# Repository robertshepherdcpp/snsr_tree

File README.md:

# snsr_tree
a tree with all the sensors you need to stay healthy!

## inspiration
- i have always wanted some sensors for my room, however, they are expensive and involve constantly checking the readings.
- so i thought it would be cool to make my own, where all these sensors are merged into one thing — and if certain levels were too high, it would actually tell me to change them!
- i wanted it to be something that sits in my room, so i decided to make it the shape of a tree (to blend in with the plants on my desk).

## how to use
1. get the PCB and case printed, and buy all the parts (listed in the BOM — total cost: $82.23)
2. paint the case green as shown in the 3D renders
3. download the audio files (mp3) from this repository and save them onto an SD card (32GB)
4. insert the SD card into the SD card holder on the PCB
5. assemble the case using screws, which also go through the PCB
6. plug into a computer and flash the firmware (in this repository) to the XIAO-ESP32-C6 — easiest via the Arduino IDE
7. keep plugged into the computer, as it is the project's power source
8. use the project and listen out for warnings!

## what it is / how it works
- the snsr_tree takes readings of different environmental levels: CO2, humidity, temperature, and light
- based on those readings, it will alert you to change certain levels — or in some cases do it for you (e.g. when it's too dark)
- keeping you informed about the conditions in your room!
  
## features
- WiFi communication for RTC (real-time clock sync)
- I2C protocol for sensor communication

## screenshots
 
the 3D case:

the schematic:

the PCB wiring:

PCB 3D model:

BOM:
| Name                      | Price  | Link                                                                                                                                                                                                                                                                                                                                                                                                                                                                                                                                                                                                                                                                                                                                                                                 |
|---------------------------|--------|--------------------------------------------------------------------------------------------------------------------------------------------------------------------------------------------------------------------------------------------------------------------------------------------------------------------------------------------------------------------------------------------------------------------------------------------------------------------------------------------------------------------------------------------------------------------------------------------------------------------------------------------------------------------------------------------------------------------------------------------------------------------------------------|
| SCD40                     | $19.60 | https://www.aliexpress.com/item/1005004251901089.html?spm=a2g0o.productlist.main.1.f0a36940xHZXsd&algo_pvid=10ce4034-62d2-442d-8264-95d3fc0cb1b9&algo_exp_id=10ce4034-62d2-442d-8264-95d3fc0cb1b9-0&pdp_ext_f=%7B%22order%22%3A%222300%22%2C%22spu_best_type%22%3A%22price%22%2C%22eval%22%3A%221%22%2C%22fromPage%22%3A%22search%22%7D&pdp_npi=6%40dis%21USD%2119.74%2119.60%21%21%2119.74%2119.60%21%40211b65de17805964801466667e7a3b%2112000028526792982%21sea%21UK%210%21ABX%211%210%21n_tag%3A-29910%3Bd%3Af52ab060%3Bm03_new_user%3A-29895%3BpisId%3A5000000208122348&curPageLogUid=Gt4emBnw6aWf&utparam-url=scene%3Asearch%7Cquery_from%3A%7Cx_object_id%3A1005004251901089%7C_p_origin_prod%3A                                                                               |
| ICS-43434                 | $3.43  | https://www.aliexpress.com/item/1005009682961260.html?spm=a2g0o.productlist.main.1.46626a32kvCDHV&algo_pvid=305191e5-e603-49bc-bde6-89f0ed3f54c3&algo_exp_id=305191e5-e603-49bc-bde6-89f0ed3f54c3-0&pdp_ext_f=%7B%22order%22%3A%22159%22%2C%22spu_best_type%22%3A%22price%22%2C%22eval%22%3A%221%22%2C%22fromPage%22%3A%22search%22%7D&pdp_npi=6%40dis%21USD%213.44%213.43%21%21%213.44%213.43%21%40211b61bb17805966838927911ebdbf%2112000049849967017%21sea%21UK%210%21ABX%211%210%21n_tag%3A-29910%3Bd%3Af52ab060%3Bm03_new_user%3A-29895%3BpisId%3A5000000206380079&curPageLogUid=vnISMVQXcKGG&utparam-url=scene%3Asearch%7Cquery_from%3A%7Cx_object_id%3A1005009682961260%7C_p_origin_prod%3A                                                                                    |
| MAX98357A Audio Amplifier | $1.32  | https://www.aliexpress.com/item/1005007003802663.html?spm=a2g0o.productlist.main.4.54db3ed2ICoh6i&aem_p4p_detail=20260604111212187207446575000000636222&algo_pvid=8bf1989e-f7b9-4b21-9828-e25bebf76112&algo_exp_id=8bf1989e-f7b9-4b21-9828-e25bebf76112-3&pdp_ext_f=%7B%22order%22%3A%221952%22%2C%22spu_best_type%22%3A%22price%22%2C%22eval%22%3A%221%22%2C%22fromPage%22%3A%22search%22%7D&pdp_npi=6%40dis%21USD%211.32%211.32%21%21%218.92%218.92%21%402103864c17805967319468117e6fd4%2112000052658790894%21sea%21UK%210%21ABX%211%210%21n_tag%3A-29910%3Bd%3Af52ab060%3Bm03_new_user%3A-29895&curPageLogUid=jVDx2fWExivP&utparam-url=scene%3Asearch%7Cquery_from%3A%7Cx_object_id%3A1005007003802663%7C_p_origin_prod%3A&search_p4p_id=20260604111212187207446575000000636222_1 |
| MCP23017                  | $1.81  | https://www.aliexpress.com/item/1005007892385986.html?spm=a2g0o.productlist.main.1.19ce148db0NMy5&algo_pvid=4fb0fba9-8dfa-42e5-b338-c460bbb00062&algo_exp_id=4fb0fba9-8dfa-42e5-b338-c460bbb00062-0&pdp_ext_f=%7B%22order%22%3A%2242%22%2C%22eval%22%3A%221%22%2C%22fromPage%22%3A%22search%22%7D&pdp_npi=6%40dis%21USD%211.81%211.36%21%21%211.81%211.36%21%4021039a5b17805968783535429ee609%2112000042742577366%21sea%21UK%210%21ABX%211%210%21n_tag%3A-29910%3Bd%3Af52ab060%3Bm03_new_user%3A-29895&curPageLogUid=5EILj2DePQUk&utparam-url=scene%3Asearch%7Cquery_from%3A%7Cx_object_id%3A1005007892385986%7C_p_origin_prod%3A                                                                                                                                                    |
| XIAO-ESP32-C6             | $7.11  | https://www.aliexpress.com/item/1005008233414789.html?spm=a2g0o.productlist.main.1.27176a0bBY3H61&algo_pvid=f83ac481-2e2f-413d-a022-672c46ecc1ce&algo_exp_id=f83ac481-2e2f-413d-a022-672c46ecc1ce-0&pdp_ext_f=%7B%22order%22%3A%2235%22%2C%22eval%22%3A%221%22%2C%22fromPage%22%3A%22search%22%7D&pdp_npi=6%40dis%21USD%2110.93%219.29%21%21%2173.66%2162.61%21%402103835c17805969320216431e20c2%2112000058240791932%21sea%21UK%210%21ABX%211%210%21n_tag%3A-29910%3Bd%3Af52ab060%3Bm03_new_user%3A-29895&curPageLogUid=3Z71R6KGLr0g&utparam-url=scene%3Asearch%7Cquery_from%3A%7Cx_object_id%3A1005008233414789%7C_p_origin_prod%3A                                                                                                                                                 |
| micro-sd card holder      | $6.74  | https://www.aliexpress.com/item/1005008118445934.html                                                                                                                                                                                                                                                                                                                                                                                                                                                                                                                                                                                                                                                                                                                                |
| speaker                   | $0.82  | https://www.lcsc.com/product-detail/C530531.html?s_z=n_q_C530531&globalKeyword=C530531                                                                                                                                                                                                                                                                                                                                                                                                                                                                                                                                                                                                                                                                                               |
| leds                      | $2.08  | https://www.aliexpress.com/item/1005010643263450.html?spm=a2g0o.productlist.main.1.45a03cdeW0oIiS&algo_pvid=94b74e18-6588-47ce-a564-686ec8469cf2&algo_exp_id=94b74e18-6588-47ce-a564-686ec8469cf2-0&pdp_ext_f=%7B%22order%22%3A%2283%22%2C%22spu_best_type%22%3A%22price%22%2C%22eval%22%3A%221%22%2C%22fromPage%22%3A%22search%22%7D&pdp_npi=6%40dis%21USD%212.33%212.09%21%21%212.33%212.09%21%402103894417805971857632365eb21f%2112000053061696690%21sea%21UK%210%21ABX%211%210%21n_tag%3A-29910%3Bd%3Af52ab060%3Bm03_new_user%3A-29895%3BpisId%3A5000000206380079&curPageLogUid=BF1YAVMOhfXj&utparam-url=scene%3Asearch%7Cquery_from%3A%7Cx_object_id%3A1005010643263450%7C_p_origin_prod%3A                                                                                     |
| resistors - 15r           | $2.72  | https://www.aliexpress.com/item/1005011892468044.html?spm=a2g0o.productlist.main.12.41b923daARaQPN&aem_p4p_detail=202606041121496780005839712470000594265&algo_pvid=64f265c9-0491-439c-a3c9-58f0f91b0dba&algo_exp_id=64f265c9-0491-439c-a3c9-58f0f91b0dba-11&pdp_ext_f=%7B%22order%22%3A%229%22%2C%22eval%22%3A%221%22%2C%22fromPage%22%3A%22search%22%7D&pdp_npi=6%40dis%21USD%212.72%212.04%21%21%2118.36%2113.77%21%40211b815c17805973094471622ed14f%2112000056918522770%21sea%21UK%210%21ABX%211%210%21n_tag%3A-29910%3Bd%3Af52ab060%3Bm03_new_user%3A-29895&curPageLogUid=lUmGxkF3KGzQ&utparam-url=scene%3Asearch%7Cquery_from%3A%7Cx_object_id%3A1005011892468044%7C_p_origin_prod%3A&search_p4p_id=202606041121496780005839712470000594265_3                                  |
| resistors - 10k           | $2.72  | https://www.aliexpress.com/item/1005011892468044.html?spm=a2g0o.productlist.main.12.41b923daARaQPN&aem_p4p_detail=202606041121496780005839712470000594265&algo_pvid=64f265c9-0491-439c-a3c9-58f0f91b0dba&algo_exp_id=64f265c9-0491-439c-a3c9-58f0f91b0dba-11&pdp_ext_f=%7B%22order%22%3A%229%22%2C%22eval%22%3A%221%22%2C%22fromPage%22%3A%22search%22%7D&pdp_npi=6%40dis%21USD%212.72%212.04%21%21%2118.36%2113.77%21%40211b815c17805973094471622ed14f%2112000056918522770%21sea%21UK%210%21ABX%211%210%21n_tag%3A-29910%3Bd%3Af52ab060%3Bm03_new_user%3A-29895&curPageLogUid=lUmGxkF3KGzQ&utparam-url=scene%3Asearch%7Cquery_from%3A%7Cx_object_id%3A1005011892468044%7C_p_origin_prod%3A&search_p4p_id=202606041121496780005839712470000594265_3                                  |
| resistors - 4.7k          | $2.72  | https://www.aliexpress.com/item/1005011892468044.html?spm=a2g0o.productlist.main.12.41b923daARaQPN&aem_p4p_detail=202606041121496780005839712470000594265&algo_pvid=64f265c9-0491-439c-a3c9-58f0f91b0dba&algo_exp_id=64f265c9-0491-439c-a3c9-58f0f91b0dba-11&pdp_ext_f=%7B%22order%22%3A%229%22%2C%22eval%22%3A%221%22%2C%22fromPage%22%3A%22search%22%7D&pdp_npi=6%40dis%21USD%212.72%212.04%21%21%2118.36%2113.77%21%40211b815c17805973094471622ed14f%2112000056918522770%21sea%21UK%210%21ABX%211%210%21n_tag%3A-29910%3Bd%3Af52ab060%3Bm03_new_user%3A-29895&curPageLogUid=lUmGxkF3KGzQ&utparam-url=scene%3Asearch%7Cquery_from%3A%7Cx_object_id%3A1005011892468044%7C_p_origin_prod%3A&search_p4p_id=202606041121496780005839712470000594265_3                                  |
| resistors - 100k          | $2.74  | https://www.aliexpress.com/item/1005011892468044.html?spm=a2g0o.productlist.main.12.41b923daARaQPN&aem_p4p_detail=202606041121496780005839712470000594265&algo_pvid=64f265c9-0491-439c-a3c9-58f0f91b0dba&algo_exp_id=64f265c9-0491-439c-a3c9-58f0f91b0dba-11&pdp_ext_f=%7B%22order%22%3A%229%22%2C%22eval%22%3A%221%22%2C%22fromPage%22%3A%22search%22%7D&pdp_npi=6%40dis%21USD%212.72%212.04%21%21%2118.36%2113.77%21%40211b815c17805973094471622ed14f%2112000056918522770%21sea%21UK%210%21ABX%211%210%21n_tag%3A-29910%3Bd%3Af52ab060%3Bm03_new_user%3A-29895&curPageLogUid=lUmGxkF3KGzQ&utparam-url=scene%3Asearch%7Cquery_from%3A%7Cx_object_id%3A1005011892468044%7C_p_origin_prod%3A&search_p4p_id=202606041121496780005839712470000594265_3                                  |
| capcitor - 100nf          | $0.76  | https://www.aliexpress.com/item/32371454429.html?spm=a2g0o.productlist.main.1.7071ClEMClEMpm&algo_pvid=c63cc112-5413-4ab8-b733-101ff16f0902&algo_exp_id=c63cc112-5413-4ab8-b733-101ff16f0902-0&pdp_ext_f=%7B%22order%22%3A%2243%22%2C%22eval%22%3A%221%22%2C%22fromPage%22%3A%22search%22%7D&pdp_npi=6%40dis%21USD%210.76%210.76%21%21%210.76%210.76%21%402103846917805976299118832ef6c7%2152762908672%21sea%21UK%210%21ABX%211%210%21n_tag%3A-29910%3Bd%3Af52ab060%3Bm03_new_user%3A-29895&curPageLogUid=dIjc8NwSzsQi&utparam-url=scene%3Asearch%7Cquery_from%3A%7Cx_object_id%3A32371454429%7C_p_origin_prod%3A                                                                                                                                                                    |
| capacitor - 10uF          | $1.24  | https://www.aliexpress.com/item/1005007137284660.html?spm=a2g0o.productlist.main.4.53be285d6mw6WQ&aem_p4p_detail=202606211419253440695899267720002691438&algo_pvid=3afa55f8-eafd-44c8-84a4-e828b7d21e5c&algo_exp_id=3afa55f8-eafd-44c8-84a4-e828b7d21e5c-3&pdp_ext_f=%7B%22order%22%3A%22238%22%2C%22eval%22%3A%221%22%2C%22fromPage%22%3A%22search%22%7D&pdp_npi=6%40dis%21USD%211.24%210.99%21%21%218.40%216.72%21%40210385db17820767651866765e09e9%2112000039535543114%21sea%21UK%210%21ABX%211%210%21n_tag%3A-29910%3Bd%3Af52ab060%3Bm03_new_user%3A-29895&curPageLogUid=9b90RMqDifxh&utparam-url=scene%3Asearch%7Cquery_from%3A%7Cx_object_id%3A1005007137284660%7C_p_origin_prod%3A&search_p4p_id=202606211419253440695899267720002691438_1                                    |
| capacitor - 4.7uF         | $1.24  | https://www.aliexpress.com/item/1005007137284660.html?spm=a2g0o.productlist.main.4.53be285d6mw6WQ&aem_p4p_detail=202606211419253440695899267720002691438&algo_pvid=3afa55f8-eafd-44c8-84a4-e828b7d21e5c&algo_exp_id=3afa55f8-eafd-44c8-84a4-e828b7d21e5c-3&pdp_ext_f=%7B%22order%22%3A%22238%22%2C%22eval%22%3A%221%22%2C%22fromPage%22%3A%22search%22%7D&pdp_npi=6%40dis%21USD%211.24%210.99%21%21%218.40%216.72%21%40210385db17820767651866765e09e9%2112000039535543114%21sea%21UK%210%21ABX%211%210%21n_tag%3A-29910%3Bd%3Af52ab060%3Bm03_new_user%3A-29895&curPageLogUid=9b90RMqDifxh&utparam-url=scene%3Asearch%7Cquery_from%3A%7Cx_object_id%3A1005007137284660%7C_p_origin_prod%3A&search_p4p_id=202606211419253440695899267720002691438_1                                    |
| capacitor - 1uF           | $1.24  | https://www.aliexpress.com/item/1005007137284660.html?spm=a2g0o.productlist.main.4.53be285d6mw6WQ&aem_p4p_detail=202606211419253440695899267720002691438&algo_pvid=3afa55f8-eafd-44c8-84a4-e828b7d21e5c&algo_exp_id=3afa55f8-eafd-44c8-84a4-e828b7d21e5c-3&pdp_ext_f=%7B%22order%22%3A%22238%22%2C%22eval%22%3A%221%22%2C%22fromPage%22%3A%22search%22%7D&pdp_npi=6%40dis%21USD%211.24%210.99%21%21%218.40%216.72%21%40210385db17820767651866765e09e9%2112000039535543114%21sea%21UK%210%21ABX%211%210%21n_tag%3A-29910%3Bd%3Af52ab060%3Bm03_new_user%3A-29895&curPageLogUid=9b90RMqDifxh&utparam-url=scene%3Asearch%7Cquery_from%3A%7Cx_object_id%3A1005007137284660%7C_p_origin_prod%3A&search_p4p_id=202606211419253440695899267720002691438_1                                    |
| ldr                       | $1.02  | https://www.aliexpress.com/item/1005004112010040.html?spm=a2g0o.productlist.main.6.23af6f92yq5fsR&algo_pvid=09979ea5-7993-4aa6-a07d-fd84de491b4f&algo_exp_id=09979ea5-7993-4aa6-a07d-fd84de491b4f-5&pdp_ext_f=%7B%22order%22%3A%22181%22%2C%22eval%22%3A%221%22%2C%22fromPage%22%3A%22search%22%7D&pdp_npi=6%40dis%21USD%211.02%210.87%21%21%211.02%210.87%21%40210390c217805977820272427e5a25%2112000057603572767%21sea%21UK%210%21ABX%211%210%21n_tag%3A-29910%3Bd%3Af52ab060%3Bm03_new_user%3A-29895&curPageLogUid=cZMJc4zObGdm&utparam-url=scene%3Asearch%7Cquery_from%3A%7Cx_object_id%3A1005004112010040%7C_p_origin_prod%3A                                                                                                                                                   |
| m2 12mm screws            | $2.11  | https://www.aliexpress.com/item/1005008143416203.html?spm=a2g0o.productlist.main.20.5d06a3ebhgJIeg&aem_p4p_detail=202606050604407891662337876140001200550&algo_pvid=59c4199c-8934-46c5-b976-56107f21c16b&algo_exp_id=59c4199c-8934-46c5-b976-56107f21c16b-19&pdp_ext_f=%7B%22order%22%3A%226453%22%2C%22eval%22%3A%221%22%2C%22fromPage%22%3A%22search%22%7D&pdp_npi=6%40dis%21USD%212.56%212.40%21%21%2117.24%2116.18%21%40211b815c17806646805545810e459e%2112000043970780509%21sea%21UK%210%21ABX%211%210%21n_tag%3A-29910%3Bd%3Af52ab060%3Bm03_new_user%3A-29895%3BpisId%3A5000000206380079&curPageLogUid=cFyM0bsjev7p&utparam-url=scene%3Asearch%7Cquery_from%3A%7Cx_object_id%3A1005008143416203%7C_p_origin_prod%3A&search_p4p_id=202606050604407891662337876140001200550_5    |
| pcb fabrication           | $10.10 | https://cart.jlcpcb.com/quote?stencilLayer=2&stencilWidth=100&stencilLength=100&stencilCounts=5&plateType=1&spm=Jlcpcb.Homepage.1010                                                                                                                                                                                                                                                                                                                                                                                                                                                                                                                                                                                                                                                 |
| shipping                  | $10.71 | https://cart.jlcpcb.com/quote?stencilLayer=2&stencilWidth=100&stencilLength=100&stencilCounts=5&plateType=1&spm=Jlcpcb.Homepage.1010                                                                                                                                                                                                                                                                                                                                                                                                                                                                                                                                                                                                                                                 |
| total cost                | $82.23 | -                                                                                                                                                                                                                                                                                                                                                                                                                                                                                                                                                                                                                                                                                                                                                                                    |

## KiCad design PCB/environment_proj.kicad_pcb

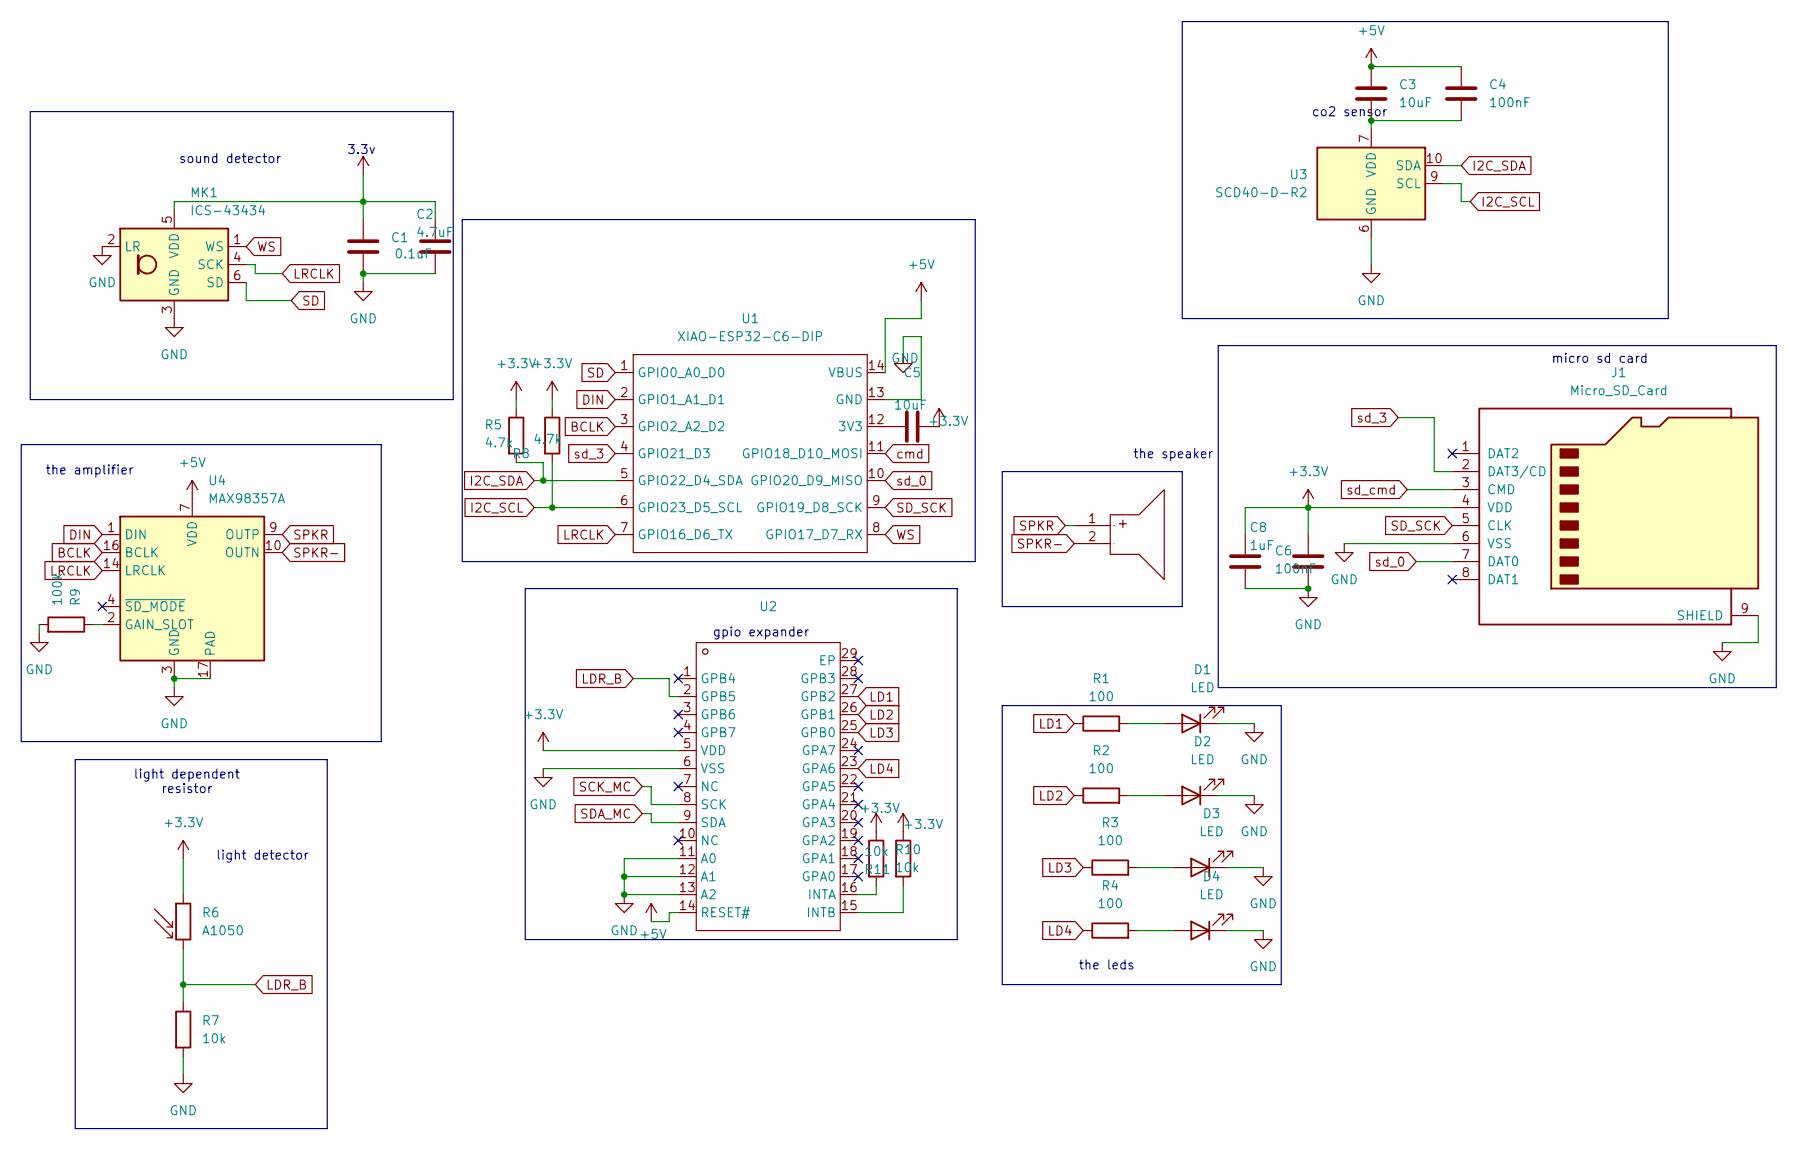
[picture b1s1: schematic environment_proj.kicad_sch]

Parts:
C1: 0.1uF; C_0603_1608Metric_Pad1.08x0.95mm_HandSolder
C2: 4.7uF; C_0603_1608Metric
C3, C5: 10uF; C_0603_1608Metric
C4, C6: 100nF; C_0603_1608Metric
C8: 1uF; C_0603_1608Metric
D1: LED; R_0603_1608Metric_Pad0.98x0.95mm_HandSolder
D2, D3, D4: LED; LED_0603_1608Metric_Pad1.05x0.95mm_HandSolder
J1: Micro_SD_Card; microSD_HC_Hirose_DM3AT-SF-PEJM5
MK1: ICS-43434; InvenSense_ICS-43434-6_3.5x2.65mm
R1, R2, R3, R4: 100; R_0603_1608Metric_Pad0.98x0.95mm_HandSolder
R5, R8: 4.7k; R_0603_1608Metric_Pad0.98x0.95mm_HandSolder
R6: A1050; R_LDR_D6.4mm_P3.4mm_Vertical
R7, R10, R11: 10k; R_0603_1608Metric_Pad0.98x0.95mm_HandSolder
R9: 100k; R_0603_1608Metric_Pad0.98x0.95mm_HandSolder
SPK4: SPK-TH_BD23.0-P10.00-D0.8-L-RD; Manufacturer Part GSPK2307P-8R1W; LCSC Part Name 23mm 8Ω
U1: XIAO-ESP32-C6-DIP
U2: QFN-28_L6.0-W6.0-P0.65-BL-EP3.7; Manufacturer Part MCP23017T-E/ML; LCSC Part Name 16位带串行接口的I/O扩展器
U3: SCD40-D-R2; Sensirion_SCD4x-1EP_10.1x10.1mm_P1.25mm_EP4.8x4.8mm
U4: MAX98357A; TQFN-16-1EP_3x3mm_P0.5mm_EP1.23x1.23mm

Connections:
+3.3V: C1.1, C2.1, C5.2, C6.1, C8.1, J1.4 (VDD), MK1.5 (VDD), R5.1, R6.1, R8.1, R10.1, R11.1, U2.5 (VDD)
+5V: C3.1, C4.1, U1.14 (VBUS), U2.14 (RESET#), U4.7 (VDD), U4.8 (VDD)
BCLK: U1.3 (GPIO2_A2_D2), U4.16 (BCLK)
DIN: U1.2 (GPIO1_A1_D1), U4.1 (DIN)
GND: C1.2, C2.2, C6.2, C8.2, D1.1 (K), D2.1 (K), D3.1 (K), D4.1 (K), J1.6 (VSS), J1.9 (SHIELD), MK1.2 (LR), MK1.3 (GND), R7.2, R9.2, U1.13 (GND), U2.6 (VSS), U2.11 (A0), U2.12 (A1), U2.13 (A2), U3.6 (GND), U3.20 (GND), U3.21 (GND), U4.3 (GND), U4.11 (GND), U4.15 (GND), U4.17 (PAD)
I2C_SCL: R8.2, U1.6 (GPIO23_D5_SCL), U3.9 (SCL)
I2C_SDA: R5.2, U1.5 (GPIO22_D4_SDA), U3.10 (SDA)
LD1: R1.1, U2.27 (GPB2)
LD2: R2.1, U2.26 (GPB1)
LD3: R3.1, U2.25 (GPB0)
LD4: R4.1, U2.23 (GPA6)
LDR_B: R6.2, R7.1, U2.2 (GPB5)
LRCLK: MK1.4 (SCK), U1.7 (GPIO16_D6_TX), U4.14 (LRCLK)
unnamed: C3.2, C4.2, U3.7 (VDD), U3.19 (VDD)
unnamed: D1.2 (A), R1.2
unnamed: D2.2 (A), R2.2
unnamed: D3.2 (A), R3.2
unnamed: D4.2 (A), R4.2
unnamed: C5.1, U1.12 (3V3)
unnamed: R10.2, U2.16 (INTA)
unnamed: R11.2, U2.15 (INTB)
unnamed: R9.1, U4.2 (GAIN_SLOT)
SCK_MC: U2.8 (SCK)
SD: MK1.6 (SD), U1.1 (GPIO0_A0_D0)
SDA_MC: U2.9 (SDA)
SD_SCK: J1.5 (CLK), U1.9 (GPIO19_D8_SCK)
SPKR: SPK4.1 (+), U4.9 (OUTP); also elsewhere on the board
SPKR-: SPK4.2 (-), U4.10 (OUTN)
WS: MK1.1 (WS), U1.8 (GPIO17_D7_RX)
cmd: U1.11 (GPIO18_D10_MOSI)
sd_0: J1.7 (DAT0), U1.10 (GPIO20_D9_MISO)
sd_3: J1.2 (DAT3/CD), U1.4 (GPIO21_D3)
sd_cmd: J1.3 (CMD)

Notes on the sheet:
the amplifier
light detector
the speaker
micro sd card
3.3v
co2 sensor
the leds
gpio expander
sound detector
light dependent resistor

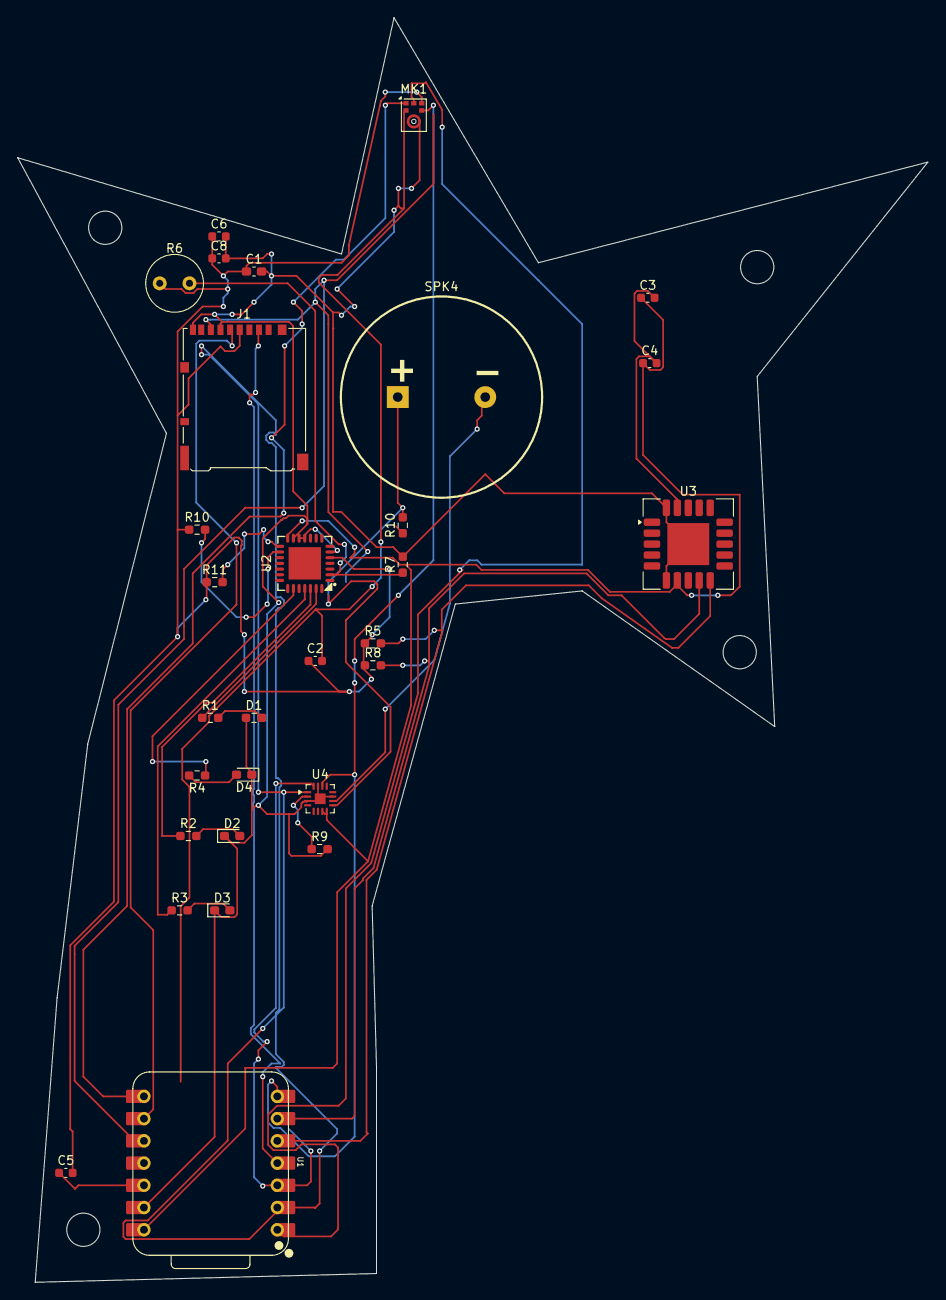
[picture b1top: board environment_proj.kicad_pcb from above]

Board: 2 copper layers, 104.0 x 144.5 mm, 30 parts (0 on the bottom side), 29 nets.

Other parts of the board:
R10#2: 8; R_0603_1608Metric_Pad0.98x0.95mm_HandSolder

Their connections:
SPKR: R10#2.2; also elsewhere on the board

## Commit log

2026-05-14 add the firmware
2026-05-14 Rename environment_proj.ino to firmware/environment_proj.ino
2026-05-14 add the actual firmware files
2026-05-14 add how to use.
2026-05-14 Enhance README with project details and features
    Added project inspiration, assembly instructions, screenshots, and features.
2026-05-14 Add PCB 3D model image to README
    Added PCB 3D model image to the README.
2026-05-14 uploading the 3d step file
2026-05-14 Rename environment_proj.step to 3d/environment_proj.step
2026-05-14 Update README with image and project inspiration
    Added an image and expanded project inspiration details.
2026-05-14 add the zine.
2026-05-14 Rename Untitled (9).pdf to zine/zine.pdf
2026-06-04 add the updated code
2026-06-04 add the pcb files
2026-06-04 add the updated step file.
2026-06-05 Update BOM with new component prices and links
2026-06-08 add the updated zine to the readme
2026-06-08 add the new zine.
2026-06-08 Rename Untitled (14).pdf to zine.pdf
2026-06-08 add the 3d files
2026-06-08 add the audio files
2026-06-08 add the new pcb files
2026-06-08 Fix typos in README.md inspiration section
    Corrected typos in the inspiration section and improved clarity.
2026-06-08 Add images for 3D case, schematic, and PCB wiring
2026-06-08 Improve README with usage and functionality details
    Updated usage instructions and added a section on how the project works.
2026-06-09 adding the updated pcb files.
2026-06-09 Rename PCB/gerber.zip to PCB/Gerber/gerber.zip
2026-06-09 add the fusion file.
2026-06-11 add the pick and place files.
2026-06-12 Rename Untitled (20).pdf to zine/zine.pdf
2026-06-12 Update usage instructions in README
    Added a step to paint the case green in the usage instructions.
2026-06-12 Update README with new image and fix typos
    Added a new image to the README and corrected typos.
2026-06-17 Refactor README structure and content
    Updated README.md to improve formatting and clarity.
2026-06-21 add the bom
2026-06-21 Update README with new images for schematic and PCB
    Added additional images for schematic and PCB wiring.
2026-06-21 Rename PCB/PICK-AND-PLACE.txt to PCB/PICK-AND-PLACE/a.txt
2026-06-21 add the pick and place files new
2026-06-21 add updated pcb files
2026-06-21 Update BOM table with new prices and links
2026-06-21 Update PCB image and BOM in README
